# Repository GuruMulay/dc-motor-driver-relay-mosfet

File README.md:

View this project on [CADLAB.io](https://cadlab.io/project/1369).

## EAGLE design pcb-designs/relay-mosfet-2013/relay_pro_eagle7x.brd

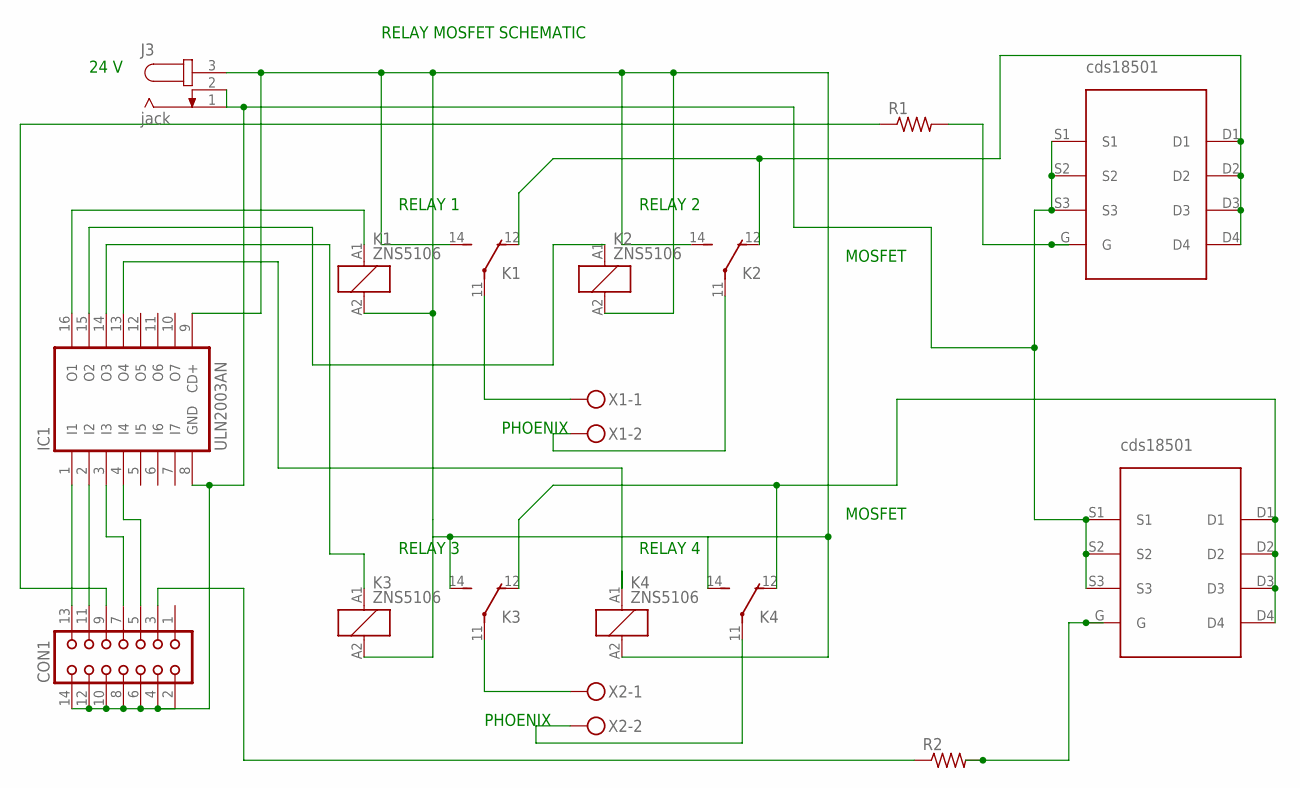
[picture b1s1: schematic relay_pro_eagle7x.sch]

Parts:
CON1: CON14
IC1: ULN2003AN; DIL16
J3: jack; SPC4077
K1, K2, K3, K4: ZNS5106; ZN5
R1, R2: R-US_R0603; R0603
U$1, U$2: CSD18503GDS-NEW; CDS
X1, X2: MKDSN1,5/2-5,08

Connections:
unnamed: K1.11, X1.1
unnamed: IC1.16 (O1), K1.A1 (1)
unnamed: K2.11, X1.2
unnamed: IC1.15 (O2), K2.A1 (1)
unnamed: K3.11, X2.1
unnamed: IC1.9 (CD+), J3.3, K1.14 (S), K1.A2 (2), K2.14 (S), K2.A2 (2), K3.14 (S), K3.A2 (2), K4.14 (S), K4.A2 (2)
unnamed: CON1.13, IC1.1 (I1)
unnamed: K4.11, X2.2
unnamed: CON1.11, IC1.2 (I2)
unnamed: CON1.7, IC1.3 (I3)
unnamed: IC1.14 (O3), K3.A1 (1)
unnamed: IC1.13 (O4), K4.A1 (1)
unnamed: CON1.9, R1.1
unnamed: K3.12 (O), K4.12 (O), U$2.D1, U$2.D2, U$2.D3, U$2.D4
unnamed: CON1.3, R2.1
unnamed: R2.2, U$2.G
unnamed: CON1.5, IC1.4 (I4)
unnamed: K1.12 (O), K2.12 (O), U$1.D1, U$1.D2, U$1.D3, U$1.D4
unnamed: R1.2, U$1.G
unnamed: CON1.2, CON1.4, CON1.6, CON1.8, CON1.10, CON1.12, CON1.14, IC1.8 (GND), J3.1, J3.2, U$1.S1, U$1.S2, U$1.S3, U$2.S1, U$2.S2, U$2.S3

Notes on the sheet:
RELAY 1
RELAY 2
RELAY 3
RELAY 4
MOSFET
PHOENIX
24 V
RELAY MOSFET SCHEMATIC

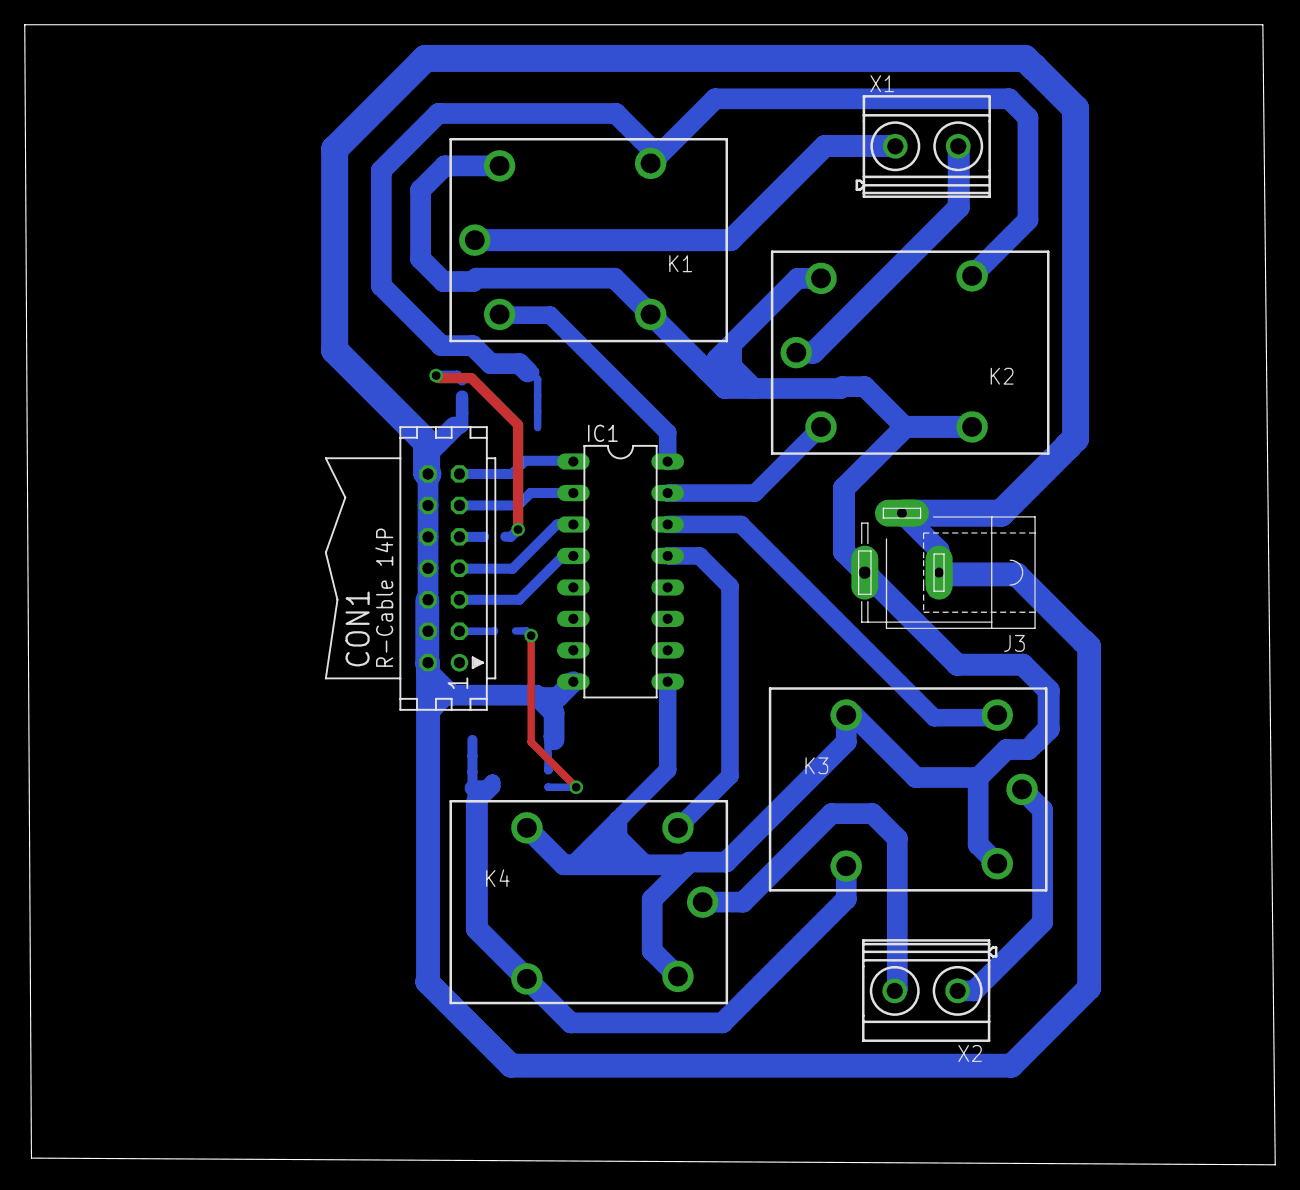
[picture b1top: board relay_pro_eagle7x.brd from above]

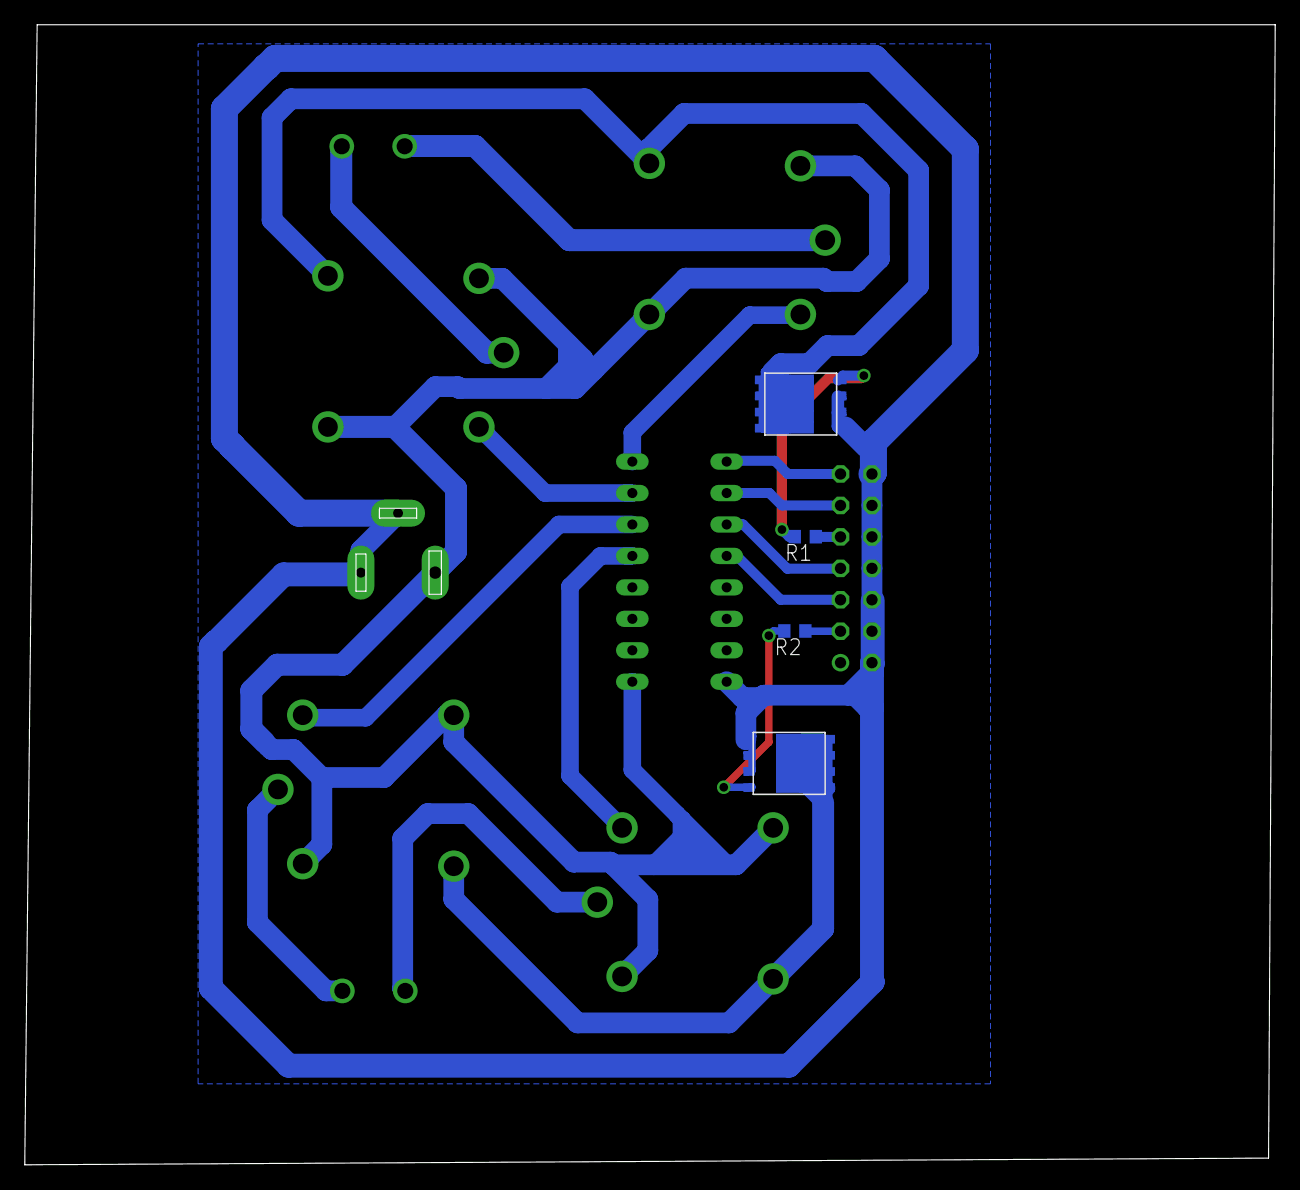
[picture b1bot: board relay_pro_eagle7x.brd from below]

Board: 2 copper layers, 101.0 x 92.1 mm, 13 parts (4 on the bottom side), 20 nets.

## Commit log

2018-10-13 init proj
2018-10-13 add 2011 version of relay mosfet motor driver
2018-10-13 add 2013 version of relay mosfet motor driver
2018-10-13 Add media
2018-10-13 adding eagle 7x compatible files
2018-10-13 Backlink to CADLAB.io has been added.
2018-10-15 Add images
2018-11-10 Add prototype images
2018-11-10 Update prototype images
